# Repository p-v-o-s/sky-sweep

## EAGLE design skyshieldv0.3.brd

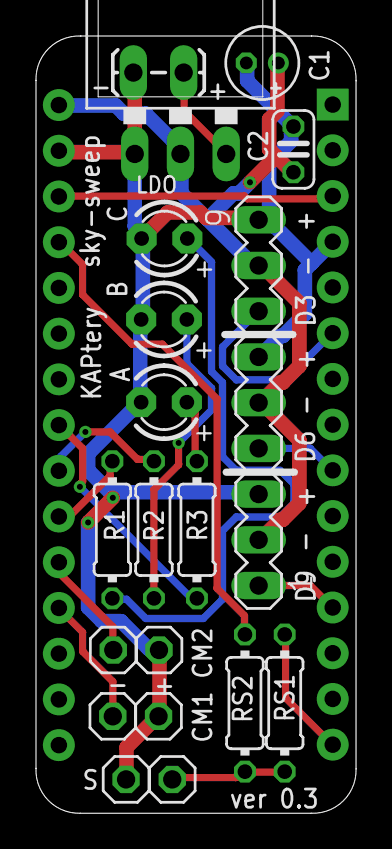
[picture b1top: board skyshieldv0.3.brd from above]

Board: 2 copper layers, 17.8 x 43.2 mm, 21 parts (0 on the bottom side), 18 nets.

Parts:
C1: 0.1µ; C025-024X044
C2: 10µ; E1,8-4
CHDK1A, CHDK1B, CHDK2A, CHDK2B: 1X01
IC1: LD117AV; TO220L1
J1: HEAD15-NOSS
J2: HEAD15-NOSS-1
JP1: BATT; 1X02_LOCK_LONGPADS
LED, LED1, LED2: POWERLED; LED3MM
R1, R2, R3: 10K; 0204/7
RS1: 100; 0204/7
RS2: 10K; 0204/7
SV4: MA09-1
SW1A, SW1B: 1X01

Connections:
+5V: J2.4, RS2.1
A0: CHDK1A.1, J2.12
A1: CHDK2A.1, J2.11
A2: J2.10, R1.1
A3: J2.9, R2.1
A4: J2.8, R3.1
D3: J1.6, SV4.7
D6: J1.9, SV4.4
D9: J1.12, SV4.1
D12/MISO: J1.15, RS1.2
GND: C1.2, C2.-, CHDK1B.1, CHDK2B.1, IC1.1, J1.4, J2.2, JP1.2, LED.K, LED1.K, LED2.K, SV4.3, SV4.6, SV4.9, SW1B.1
unnamed: LED2.A, R3.2
unnamed: LED1.A, R2.2
unnamed: LED.A, R1.2
unnamed: RS1.1, RS2.2, SW1A.1
unnamed: IC1.3, JP1.1
RESET: J1.3, J2.3
VCC: C1.1, C2.+, IC1.2, J2.1, SV4.2, SV4.5, SV4.8

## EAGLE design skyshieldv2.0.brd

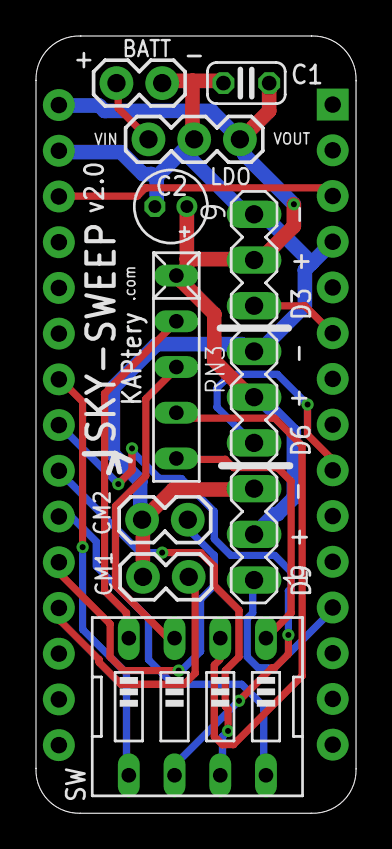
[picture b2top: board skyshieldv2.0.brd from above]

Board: 2 copper layers, 17.8 x 43.2 mm, 11 parts (0 on the bottom side), 17 nets.

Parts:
BATT: 1X02
C1: 0.1µ; C025-024X044
C2: 10µ; E1,8-4
CHDKA: 1X02
CHDKB: 1X02
J1: HEAD15-NOSS
J2: HEAD15-NOSS-1
LDO-5V: LF50ABV-DG; 1X03
RN3: RN-5
SV4: MA09-1
SW1: EDG-04

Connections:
A0: CHDKA.2, J2.12
A1: CHDKB.2, J2.11
A2: J2.10, SW1.8
A3: J2.9, SW1.7
A4: J2.8, SW1.6
A5: J2.7, SW1.5
D3: J1.6, SV4.7
D6: J1.9, SV4.4
D9: J1.12, SV4.1
GND: BATT.2, C1.2, C2.-, CHDKA.1, CHDKB.1, J1.4, J2.2, LDO-5V.2, SV4.3, SV4.6, SV4.9
unnamed: RN3.2, SW1.4
unnamed: BATT.1, LDO-5V.3
unnamed: RN3.3, SW1.3
unnamed: RN3.4, SW1.2
unnamed: RN3.5, SW1.1
RESET: J1.3, J2.3
VCC: C1.1, C2.+, J2.1, LDO-5V.1, RN3.1, SV4.2, SV4.5, SV4.8

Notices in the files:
parts and their libraries:
SparkFun-Connectors: Licensing: Creative Commons ShareAlike 4.0 International - https://creativecommons.org/licenses/by-sa/4.0
